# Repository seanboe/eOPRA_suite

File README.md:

# eOPRA_suite

Contains the board files (KiCAD + gerbers) and CLI for the eOPRA device control suite used in research on transfemoral and transtibial prosthetics
at the MIT Biomechatronics Lab.

Testing 123

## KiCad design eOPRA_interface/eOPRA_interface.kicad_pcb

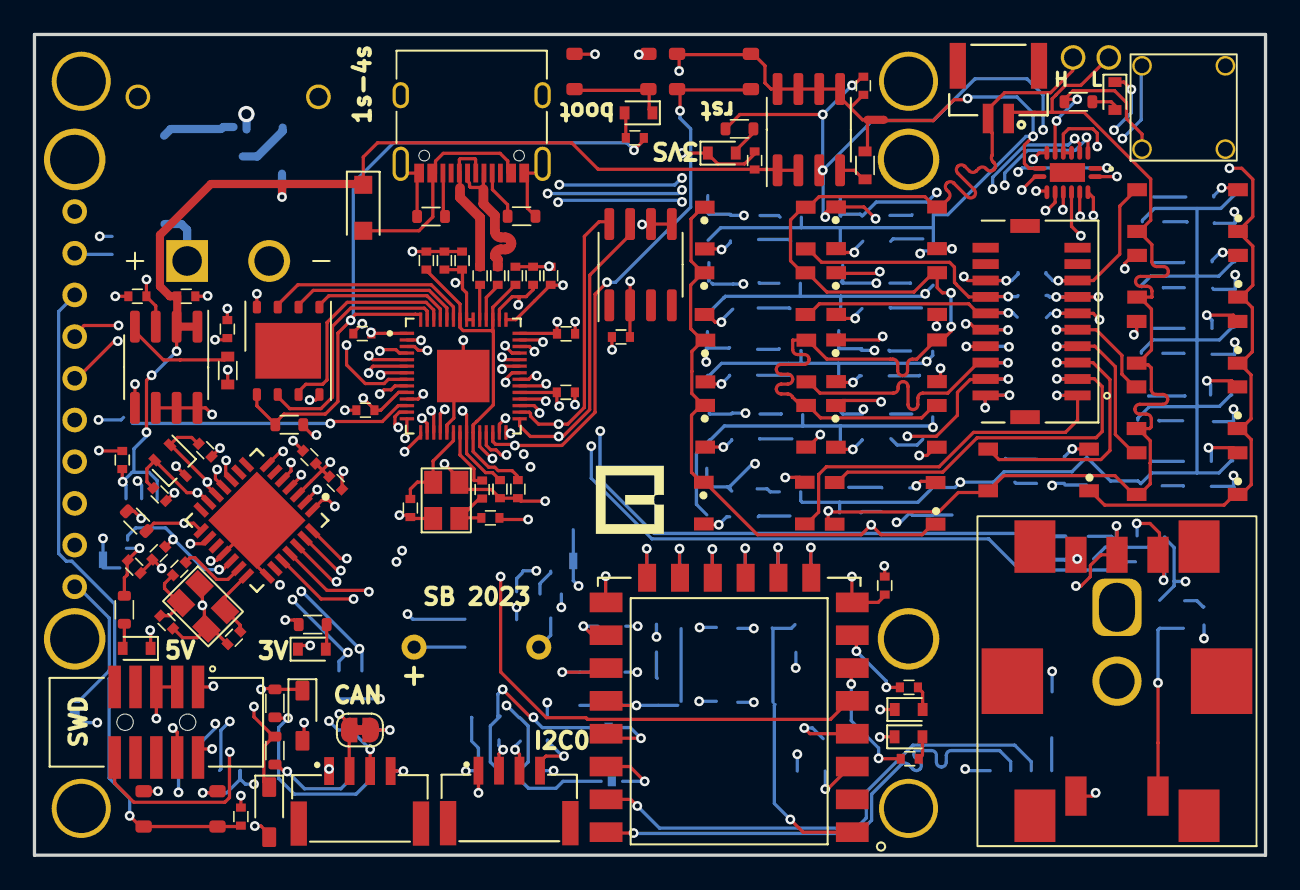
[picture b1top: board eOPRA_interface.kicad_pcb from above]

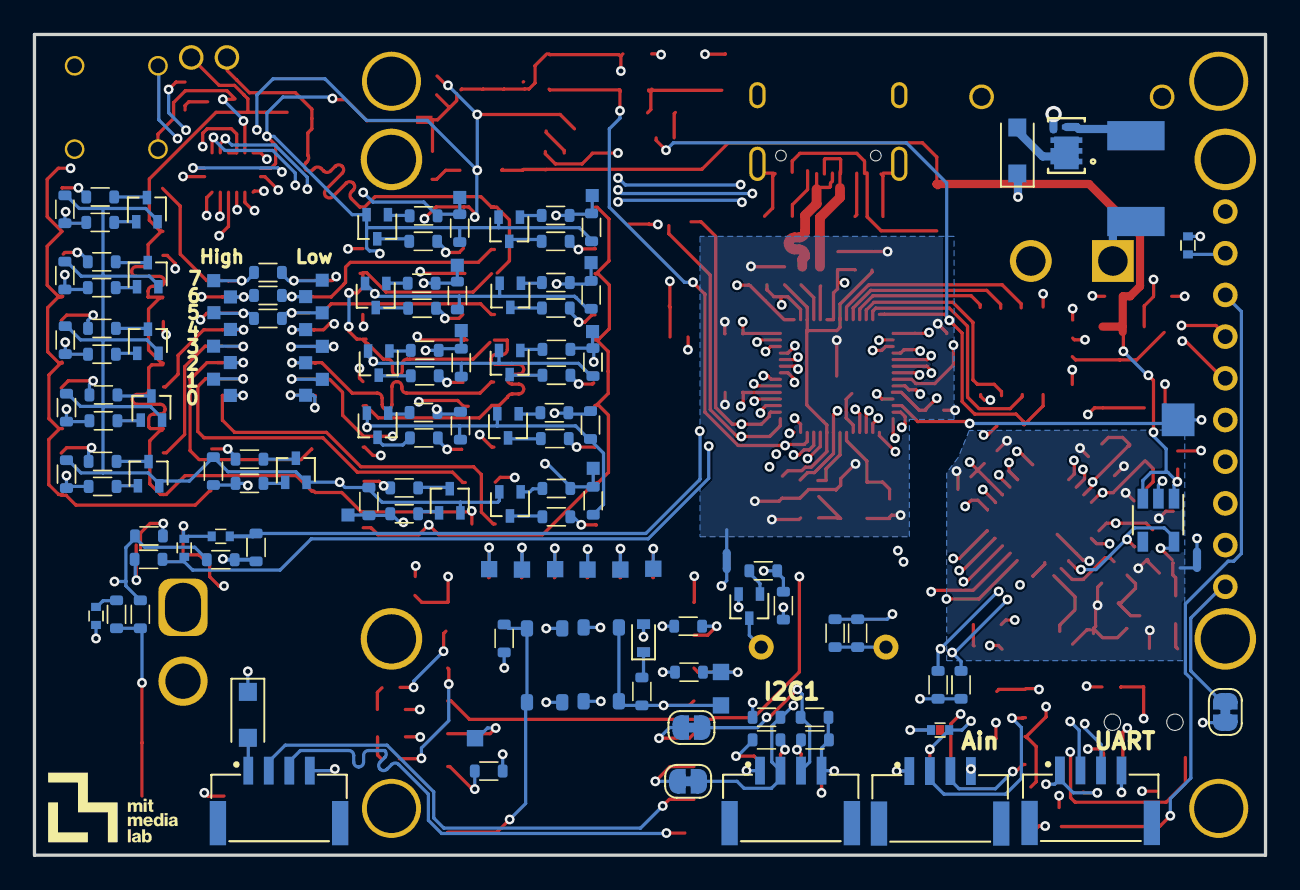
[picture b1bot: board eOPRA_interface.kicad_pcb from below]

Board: 4 copper layers, 75.0 x 50.0 mm, 254 parts (147 on the bottom side), 185 nets.

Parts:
C1, C3, C6, C16, C17, C19, C20, C28, C30, C31, C32, C33, C34, C36: 1uF; C_1005_402_A
C2, C29: 100pF; C_1608_603_B
C4, C5, C21, C22: 22pF; C_1005_402_A
C7, C8, C9, C10, C11, C12, C13, C14, C15, C18, C25, C26, C27, C35: 0.1uF; C_1005_402_A
C23, C24: 47pF; C_1005_402_A
D1: PESD1CAN; SOT-323_SC-70
D2, D4, D5: D_Schottky; D_SOD-123F
D3, D6, D7, D10, D11, D12, D13, D14: LED; D_0603
D8, D9: D_Zener; SOD-323
F1: Fuse; PTC
J1, J2, J3, J5, J7, J8: CONN_01X04_MALE; JST_SM04B-GHS-TB(LF)(SN)-
J4: CONN_01X02_MALE; JST_SM02B_GHS_TB
J6: CONN_02X10; MOLEX_2035642017
JP1, JP2, JP3, JP4: SolderJumper-2_P1.3mm_Bridged_RoundedPad1.0x1.5mm
NT1, NT2, NT3: net-tie; NetTie-2_SMD_Pad0.5mm
Q1, Q7, Q9, Q11, Q14, Q15, Q17, Q18, Q20, Q22, Q23, Q26, Q27, Q30, Q31, Q34: G3VM-351VY1-TR05
Q2, Q3, Q4, Q6, Q8, Q10, Q12, Q13, Q16, Q19, Q21, Q24, Q25, Q28, Q29, Q32, Q33: RU1J002YNTCL; SOT-323FL
Q5: Q_PMOS_GSD; SON_8DU-T1-GE3_VIS
R1, R2: 5k1; R_1608_603_B
R3, R6, R11, R13, R14, R15, R16, R19, R20, R22, R25, R27, R28, R30, R33, R36, R39, R40, R45, R50, R52, R57, R58, R63, R64, R69, R70, R75, R76, R77, R78, R79, R82, R83: 10k; R_1608_603_B
R4, R17, R18: 1k; R_1005_402_A
R5, R7, R8, R26, R29, R31, R32, R34, R35, R37, R38, R41, R42, R43, R44, R46, R47, R48, R49, R51, R53, R54, R55, R56, R59, R60, R61, R62, R65, R66, R67, R68, R71, R72, R73, R74, R89, R90, R91: 300; R_1608_603_B
R9, R10, R12, R21: 4k7; R_1608_603_B
R23, R24: 27.4; R_1005_402_A
R80, R84, R86: 120; R_1005_402_A
R81: 500; R_1005_402_A
R85, R87, R88: N/A; R_1608_603_B
SP1: buzzer; BUZZER
SW1, SW2, SW3, SW5, SW6: SW_Push; TL3365AF180QG
SW4: AS11AH
SW7: Rotary_Encoder_Switch; PEC11S-929K-S0015
TP1, TP3, TP5, TP6, TP7, TP8, TP9, TP11, TP12: TEST; test_point_1.0mm_square
TP2: test_point_2mm_square
TP4, TP10: TEST; plated_hole_1.1x1.5mm
TP13, TP14, TP15, TP16, TP17, TP18, TP19, TP20, TP21, TP22, TP23, TP24, TP25, TP26, TP27, TP28, TP29, TP30, TP31, TP32, TP33, TP34, TP35, TP36: test_point_0.8mm_square
U1: USB_C_2.0; USB_C_XKB_U262-16XN-4BVC11
U2: ARM-SWD-10
U3, U15: AP2213-8_SOIC; SOIC-8_3.9x4.9mm_P1.27mm
U4: DS3231MZ+; SOIC-8_3.9x4.9mm_P1.27mm
U5: XT-X; AMASS_XT30PW-M
U6, U7, U8, U9: Mounting-holes; plated_hole_3.0x3.6mm
U10: RP2040; QFN40P700X700X90-57N
U11: W25Q128JVP; GD25Q16CWIGR
U12: TFT_BOB
U13: MCP25625; QFN6x6_P65
U14: AP2205-50; TSOT-23-5
U16: ESP8266-12E_ESP-12E
U17: QFN50P250X350X100-17N
Y1: 16Mhz 12pF; 4-smd
Y3: 12Mhz 12pF; 4-smd

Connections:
+1V1: C14.1, C15.1, C16.1, U10.23 (DVDD), U10.45 (VREG_VOUT), U10.50 (DVDD)
+3V3: C3.1, C7.1, C8.1, C9.1, C10.1, C11.1, C12.1, C13.1, C17.1, C18.2, C25.1, C31.2, C32.2, C33.1, C34.1, C35.2, D2.1 (K), D6.2 (A), J1.4, J2.4, J3.1, J5.4, J8.4, JP1.2, R8.1, R9.2, R10.2, R11.2, R12.2, R16.2, R18.1, R20.1, R21.2, R22.1, R25.1, R51.2, R77.1, R78.2, R79.2, R83.1, R90.2, U2.1 (Vref), U3.3 (VOUT), U4.2 (VCC), U10.1 (IOVDD), U10.10 (IOVDD), U10.22 (IOVDD), U10.33 (IOVDD), U10.42 (IOVDD), U10.43 (ADC_AVDD), U10.44 (VREG_VIN), U10.48 (USB_VDD), U10.49 (IOVDD), U11.8 (VCC), U12.9 (VCC), U13.3 (VDD), U13.11 (VIO), U16.8 (VCC)
+5V: C19.2, C20.1, R91.2, U13.19 (VDDA), U14.5 (VOUT)
+BATT: D5.2 (A), Q5.2 (S)
/A_IN_2: J3.2, R27.1
/A_IN_3: J3.3, R28.1
/BUZZER: R6.2, R7.2, U10.11 (GPIO8)
/CAN_H: C24.2, D1.2 (A2), J5.3, R80.2, U13.13 (CANH)
/CAN_L: C23.2, D1.1 (A1), J5.2, JP4.1, U13.12 (CANL)
/ENC_BUTTON: C36.2, R13.2
/ESP-Wifi/EN: R83.2, U16.3 (EN)
/ESP-Wifi/ESP_INT: U10.9 (GPIO7), U16.5 (IO14)
/ESP-Wifi/GPIO0: R14.2, SW1.1, SW1.3, TP9.1, U16.18 (IO0)
/ESP-Wifi/GPIO2: R20.2, TP1.1, U16.17 (IO2)
/ESP-Wifi/LED1: R86.2, U16.6 (IO12)
/ESP-Wifi/LED2: R84.2, U16.7 (IO13)
/ESP-Wifi/~RESET: R22.2, SW5.1, SW5.3, U16.1 (RESET)
/MISO0: U10.6 (GPIO4), U12.2 (MISO)
/MOSI0: U10.5 (GPIO3), U12.4 (MOSI)
/ROT_ENC_0: C26.1, R75.2, U10.36 (GPIO24)
/ROT_ENC_1: C27.1, R76.1, U10.37 (GPIO25)
/RX: J1.2, U10.3 (GPIO1)
/RXD: J7.2, U16.21 (RXD)
/SCK0: U10.4 (GPIO2), U12.3 (SCK)
/SCL0: J8.2, R10.1, U10.32 (GPIO21)
/SCL1: J2.2, JP2.1, R21.1, U4.8 (SCL), U10.30 (GPIO19)
/SDA0: J8.3, R9.1, U10.31 (GPIO20)
/SDA1: J2.3, JP3.1, R12.1, U4.7 (SDA), U10.29 (GPIO18)
/SD_CS: U10.8 (GPIO6), U12.6 (SD_CS)
/SWCLK: U2.4 (SWDCLK/TCK), U10.24 (SWCLK)
/SWDIO: U2.2 (SWDIO/TMS), U10.25 (SWD)
/TFT_CS: TP2.1, U10.12 (GPIO9), U12.5 (TFT_CS)
/TFT_DC: U10.7 (GPIO5), U12.7 (D/C)
/TX: J1.3, U10.2 (GPIO0)
/TXD: J7.3, U16.22 (TXD)
/USB_D+: R23.1, U1.A6 (D+), U1.B6 (D+)
/USB_D-: R24.1, U1.A7 (D-), U1.B7 (D-)
/peripherals/switch: R13.1, R79.1, SW7.S1
/peripherals/~TFT_RESET: R18.2, SW3.1, SW3.3, U12.8 (~RESET)
/processor/A_IN_2_PIN: D8.1 (K), R27.2, U10.38 (GPIO26_ADC0)
/processor/A_IN_3_PIN: D9.1 (K), R28.2, U10.39 (GPIO27_ADC1)
/processor/CAN_CS: R11.1, U10.40 (GPIO28_ADC2), U13.1 (~CS)
/processor/CAN_INT: U10.34 (GPIO22), U13.25 (~INT)
/processor/CAN_RESET: R25.2, U10.41 (GPIO29_ADC3), U13.2 (~RESET)
/processor/CAN_STBY: R15.1, U10.27 (GPIO16), U13.15 (STBY)
/processor/ENC_CTL_0: U10.16 (GPIO13), U17.1 (A0)
/processor/ENC_CTL_1: U10.17 (GPIO14), U17.2 (A1)
/processor/ENC_CTL_2: U10.18 (GPIO15), U17.3 (A2)
/processor/MISO1: U10.15 (GPIO12), U13.28 (MISO)
/processor/MOSI1: U10.14 (GPIO11), U13.27 (MOSI)
/processor/QSPI_CS: R16.1, R17.1, U10.56 (QSPI_SS), U11.1 (~CS)
/processor/QSPI_SCLK: U10.52 (QSPI_SCLK), U11.6 (CLK)
/processor/QSPI_SD0: U10.53 (QSPI_SD0), U11.5 (DI(IO0))
/processor/QSPI_SD1: U10.55 (QSPI_SD1), U11.2 (DO(IO1))
/processor/QSPI_SD2: U10.54 (QSPI_SD2), U11.3 (WP(IO2))
/processor/QSPI_SD3: U10.51 (QSPI_SD3), U11.7 (HOLD(IO3))
/processor/SCK1: U10.13 (GPIO10), U13.26 (SCK)
/processor/~Rx0BF: U10.35 (GPIO23), U13.24 (~Rx0BF)
/processor/~Tx0RTS: U10.28 (GPIO17), U13.7 (~Tx0RTS)
/regulator/SYS_PWR: C1.2, C6.2, C28.2, D4.1 (K), D5.1 (K), U3.1 (EN), U3.2 (VIN), U14.1 (VIN), U14.3 (EN), U15.1 (EN), U15.2 (VIN)
/switch_control/CHAN_0: R3.2, R26.2, R30.2, R31.2, TP29.1, U17.15 (Y0)
/switch_control/CHAN_1: R19.2, R39.2, R41.2, R46.2, TP30.1, U17.14 (Y1)
/switch_control/CHAN_2: R33.2, R34.2, R36.2, R37.2, TP31.1, U17.13 (Y2)
/switch_control/CHAN_3: R40.2, R42.2, R45.2, R47.2, TP32.1, U17.12 (Y3)
/switch_control/CHAN_4: R50.2, R53.2, R57.2, R59.2, TP33.1, U17.11 (Y4)
/switch_control/CHAN_5: R63.2, R65.2, R69.2, R71.2, TP34.1, U17.10 (Y5)
/switch_control/CHAN_6: R52.2, R54.2, R58.2, R60.2, TP35.1, U17.9 (Y6)
/switch_control/CHAN_7: R64.2, R66.2, R70.2, R72.2, TP36.1, U17.7 (Y7)
/~RESET: SW6.1, SW6.3, U2.10 (~RESET), U10.26 (~RUN)
CHAN_0A_OUT: J6.1, Q1.3, TP13.1
CHAN_0B_OUT: J6.2, Q7.3, TP14.1
CHAN_1A_OUT: J6.3, Q14.3, TP15.1
CHAN_1B_OUT: J6.4, Q17.3, TP16.1
CHAN_2A_OUT: J6.5, Q9.3, TP20.1
CHAN_2B_OUT: J6.6, Q11.3, TP19.1
CHAN_3A_OUT: J6.7, Q15.3, TP18.1
CHAN_3B_OUT: J6.8, Q18.3, TP17.1
CHAN_4A_OUT: J6.9, Q20.3, TP21.1
CHAN_4B_OUT: J6.10, Q22.3, TP22.1
CHAN_5A_OUT: J6.11, Q26.3, R88.2, TP23.1
CHAN_5B_OUT: J6.12, Q30.3, R88.1, TP24.1
CHAN_6A_OUT: J6.13, Q23.3, R85.2, TP28.1
CHAN_6B_OUT: J6.14, Q27.3, R85.1, TP27.1
CHAN_7A_OUT: J6.15, Q31.3, R87.2, TP26.1
CHAN_7B_OUT: J6.16, Q34.3, R87.1, TP25.1
EMG_HIGH: J4.1, Q1.4, Q9.4, Q14.4, Q15.4, Q20.4, Q23.4, Q26.4, Q31.4, TP4.1
EMG_LOW: J4.2, Q7.4, Q11.4, Q17.4, Q18.4, Q22.4, Q27.4, Q30.4, Q34.4, TP10.1
GND: C1.1, C2.2, C3.2, C6.1, C18.1, C26.2, C27.2, C28.1, C29.2, C30.2, C31.1, C32.1, C34.2, C36.1, D7.1 (K), D8.2 (A), D9.2 (A), D11.1 (K), D12.1 (K), D13.1 (K), J1.1, J2.1, J3.4, J5.1, J7.4, J8.1, NT1.2, NT2.2, NT3.2, Q3.2 (S), Q5.1 (G), R1.1, R2.2, R6.1, R82.2, SW1.2, SW1.4, SW2.2, SW2.4, SW3.2, SW3.4, SW5.2, SW5.4, SW6.2, SW6.4, SW7.C, SW7.S2, U1.A1 (GND), U1.A12 (GND), U1.B1 (GND), U1.B12 (GND), U1.S1 (SHIELD), U2.3 (GND), U2.5 (GND), U3.5 (GND), U3.6 (GND), U3.7 (GND), U3.8 (GND), U4.5 (GND), U4.6 (VBAT), U5.1 (-), U11.4 (GND), U12.10 (GND), U14.2 (GND), U15.5 (GND), U15.6 (GND), U15.7 (GND), U15.8 (GND), U16.15 (GND)
GNDISO1: C4.1, C5.2, C7.2, C8.2, C9.2, C10.2, C11.2, C12.2, C13.2, C14.2, C15.2, C16.2, C17.2, C25.2, NT1.1, U10.19 (TESTEN), U10.57 (GND), Y3.2, Y3.4
GNDISO2: C19.1, C20.2, C21.2, C22.1, C23.1, C24.1, C33.2, C35.1, D1.3 (common), D14.1 (K), NT3.1, R15.2, U13.18 (VSS), U13.22 (GND), U13.29 (EP), Y1.2, Y1.4
GNDREF: D10.1 (K), NT2.1, Q2.2 (S), Q4.2 (S), Q6.2 (S), Q8.2 (S), Q10.2 (S), Q12.2 (S), Q13.2 (S), Q16.2 (S), Q19.2 (S), Q21.2 (S), Q24.2 (S), Q25.2 (S), Q28.2 (S), Q29.2 (S), Q32.2 (S), Q33.2 (S), R3.1, R19.1, R30.1, R33.1, R36.1, R39.1, R40.1, R45.1, R50.1, R52.1, R57.1, R58.1, R63.1, R64.1, R69.1, R70.1, U17.4 (~G2A), U17.5 (~G2B), U17.8 (GND)
unnamed: C5.1, R4.1, Y3.1
unnamed: C21.1, R81.1, Y1.1
unnamed: D2.2 (A), J7.1
unnamed: D3.2 (A), R17.2
unnamed: D3.1 (K), SW2.1, SW2.3
unnamed: D6.1 (K), R14.1
unnamed: D7.2 (A), R89.1
unnamed: D10.2 (A), R29.1
unnamed: D11.2 (A), R84.1
unnamed: D12.2 (A), R86.1
unnamed: D13.2 (A), R90.1
unnamed: D14.2 (A), R91.1
unnamed: JP4.2, R80.1
unnamed: Q1.2, R5.2
unnamed: Q2.3 (D), R5.1
unnamed: Q2.1 (G), R26.1
unnamed: Q3.3 (D), SP1.2 (-)
unnamed: Q3.1 (G), R7.1
unnamed: Q4.3 (D), R48.1
unnamed: Q4.1 (G), R46.1
unnamed: F1.2, Q5.3 (D)
unnamed: Q6.3 (D), R32.1
unnamed: Q6.1 (G), R31.1
unnamed: Q7.2, R32.2
unnamed: Q8.3 (D), R35.1
unnamed: Q8.1 (G), R34.1
unnamed: Q9.2, R35.2
unnamed: Q10.3 (D), R38.1
unnamed: Q10.1 (G), R37.1
unnamed: Q11.2, R38.2
unnamed: Q12.3 (D), R43.1
unnamed: Q12.1 (G), R41.1
unnamed: Q13.3 (D), R44.1
unnamed: Q13.1 (G), R42.1
unnamed: Q14.2, R43.2
unnamed: Q15.2, R44.2
unnamed: Q16.3 (D), R49.1
unnamed: Q16.1 (G), R47.1
unnamed: Q17.2, R48.2
unnamed: Q18.2, R49.2
unnamed: Q19.3 (D), R55.1
unnamed: Q19.1 (G), R53.1
unnamed: Q20.2, R55.2
unnamed: Q21.3 (D), R56.1
unnamed: Q21.1 (G), R54.1
unnamed: Q22.2, R61.2
unnamed: Q23.2, R56.2
unnamed: Q24.3 (D), R61.1
unnamed: Q24.1 (G), R59.1
unnamed: Q25.3 (D), R62.1
unnamed: Q25.1 (G), R60.1
unnamed: Q26.2, R67.2
unnamed: Q27.2, R62.2
unnamed: Q28.3 (D), R67.1
unnamed: Q28.1 (G), R65.1
unnamed: Q29.3 (D), R68.1
unnamed: Q29.1 (G), R66.1
unnamed: Q30.2, R73.2
unnamed: Q31.2, R68.2
unnamed: Q32.3 (D), R73.1
unnamed: Q32.1 (G), R71.1
unnamed: Q33.3 (D), R74.1
unnamed: Q33.1 (G), R72.1
unnamed: Q34.2, R74.2
unnamed: R75.1, R78.1, SW7.A
unnamed: R76.2, R77.2, SW7.B
unnamed: R8.2, R51.1, SP1.1 (+)
unnamed: R29.2, SW4.1 (A), U17.6 (G1)
unnamed: R2.1, U1.A5 (CC1)
unnamed: R1.2, U1.B5 (CC2)
unnamed: C2.1, U3.4 (BYP)
unnamed: F1.1, U5.2 (+)
unnamed: R23.2, U10.47 (USB_D+)
unnamed: R24.2, U10.46 (USB_D-)
unnamed: C4.2, U10.20 (XIN), Y3.3
unnamed: R4.2, U10.21 (XOUT)
unnamed: JP1.1, U12.1 (LITE)
unnamed: C22.2, U13.21 (OSC1), Y1.3
unnamed: R81.2, U13.20 (OSC2)
unnamed: U13.5 (RxCAN), U13.10 (RXD)
unnamed: U13.4 (TxCAN), U13.16 (TXD)
unnamed: C29.1, U15.4 (BYP)
unnamed: TP6.1, U16.9 (CS0)
unnamed: JP3.2, U16.19 (IO4)
unnamed: JP2.2, U16.20 (IO5)
unnamed: TP11.1, U16.11 (IO9)
unnamed: TP12.1, U16.12 (IO10)
unnamed: R82.1, U16.16 (IO15)
unnamed: TP3.1, U16.4 (IO16)
unnamed: TP8.1, U16.10 (MISO)
unnamed: TP7.1, U16.13 (MOSI)
unnamed: TP5.1, U16.14 (SCLK)
SWITCHING_3V3: C30.1, Q1.1, Q7.1, Q9.1, Q11.1, Q14.1, Q15.1, Q17.1, Q18.1, Q20.1, Q22.1, Q23.1, Q26.1, Q27.1, Q30.1, Q31.1, Q34.1, R89.2, SW4.2 (B), U15.3 (VOUT), U17.16 (VDD)
VUSB: D4.2 (A), U1.A4 (VBUS), U1.A9 (VBUS), U1.B4 (VBUS), U1.B9 (VBUS)

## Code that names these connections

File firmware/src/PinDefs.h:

#ifndef PINDEFS_H
#define PINDEFS_H

// For board version 1

//**** COMMUNICATION ****

// SERIAL
#define EXT_TX        0
#define EXT_RX        1

// I2C
// Port on which switcher is the master
#define SLAVE_SDA1    18
#define SLAVE_SCL1    19

// Port on which switcher is a slave
#define MASTER_SDA0   20
#define MASTER_SCL0   21

// SPI
#define EXT_SWCK1      10
#define EXT_MOSI1      11
#define EXT_MISO1      12

// CAN
#define CAN_STBY      16
#define TX0RTS        17
#define CAN_INT       22
#define RX0BF         23
#define CAN_CS        28
#define CAN_RESET     27


//**** PERIPEHRALS ****

// ESP8266 INTERRUPT LINE
#define ESP_INT       7

// BUZZER
#define BUZZER        8

// TFT
#define TFT_DC        5
#define SD_CS         6
#define TFT_SCK0      2
#define TFT_MOSI0     3
#define TFT_MISO0     4
#define TFT_CS        9         // CAN ALSO ACT AS RP2040 SLAVE CS
#define TFT_RESET     -1        // -1 means unused

// DECODER
#define ENC_CTL_0     13
#define ENC_CTL_1     14
#define ENC_CTL_2     15

// ENCODER
#define ROT_ENC_0     24
#define ROT_ENC_1     25

// ANALOG IN
#define A_IN_2_PIN    26
#define A_IN_3_PIN    27

#endif

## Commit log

2023-07-26 first
2023-07-26 updated gitignore
2023-07-27 testing
2023-07-27 asdf
2023-08-01 schematic v1.0 finished
2023-08-01 Version updates
2023-08-04 starting layout
2023-08-14 before esp
2023-08-15 before 4 layer
2023-08-16 preliminary finish
2023-08-17 draft 2 wifi finish
2023-08-30 stuff
2023-09-06 stuffs
2023-10-02 BOARD V1 FINAL
2023-10-02 fixed mounting holes
2023-10-06 initial state
2023-10-11 I'm trying
2023-10-11 Serial problem solved
2023-10-11 Serial byte read problem solved
2023-10-11 CLI cleanup updates
2023-10-11 Initial infrastructure finished
2023-10-14 windows struggles
2023-10-18 initial
2023-10-18 i2c working
    seems to be an issue in Wire.cpp - the pin defaults to the values in `pins_arduino.h` and setSDA / setSCL results in a crash - not sure why.
2023-10-19 working
2023-10-21 Intermediate - uncomment loop and setup
2023-10-21 Lots of random crap
2023-11-28 pcb files zip
2023-11-28 connection script + stupid stuff working
2023-11-28 update
    solution is to send data and receive with onReceive and to request data immediately after so that slave has an interface over which to send data back
2023-12-01 Big updates - NOT TESTED
2023-12-02 Stuff working
2023-12-03 gitignore
2024-06-20 switch port on interrupt
2024-06-24 fsr -> switch comms working for 6/24 testing
